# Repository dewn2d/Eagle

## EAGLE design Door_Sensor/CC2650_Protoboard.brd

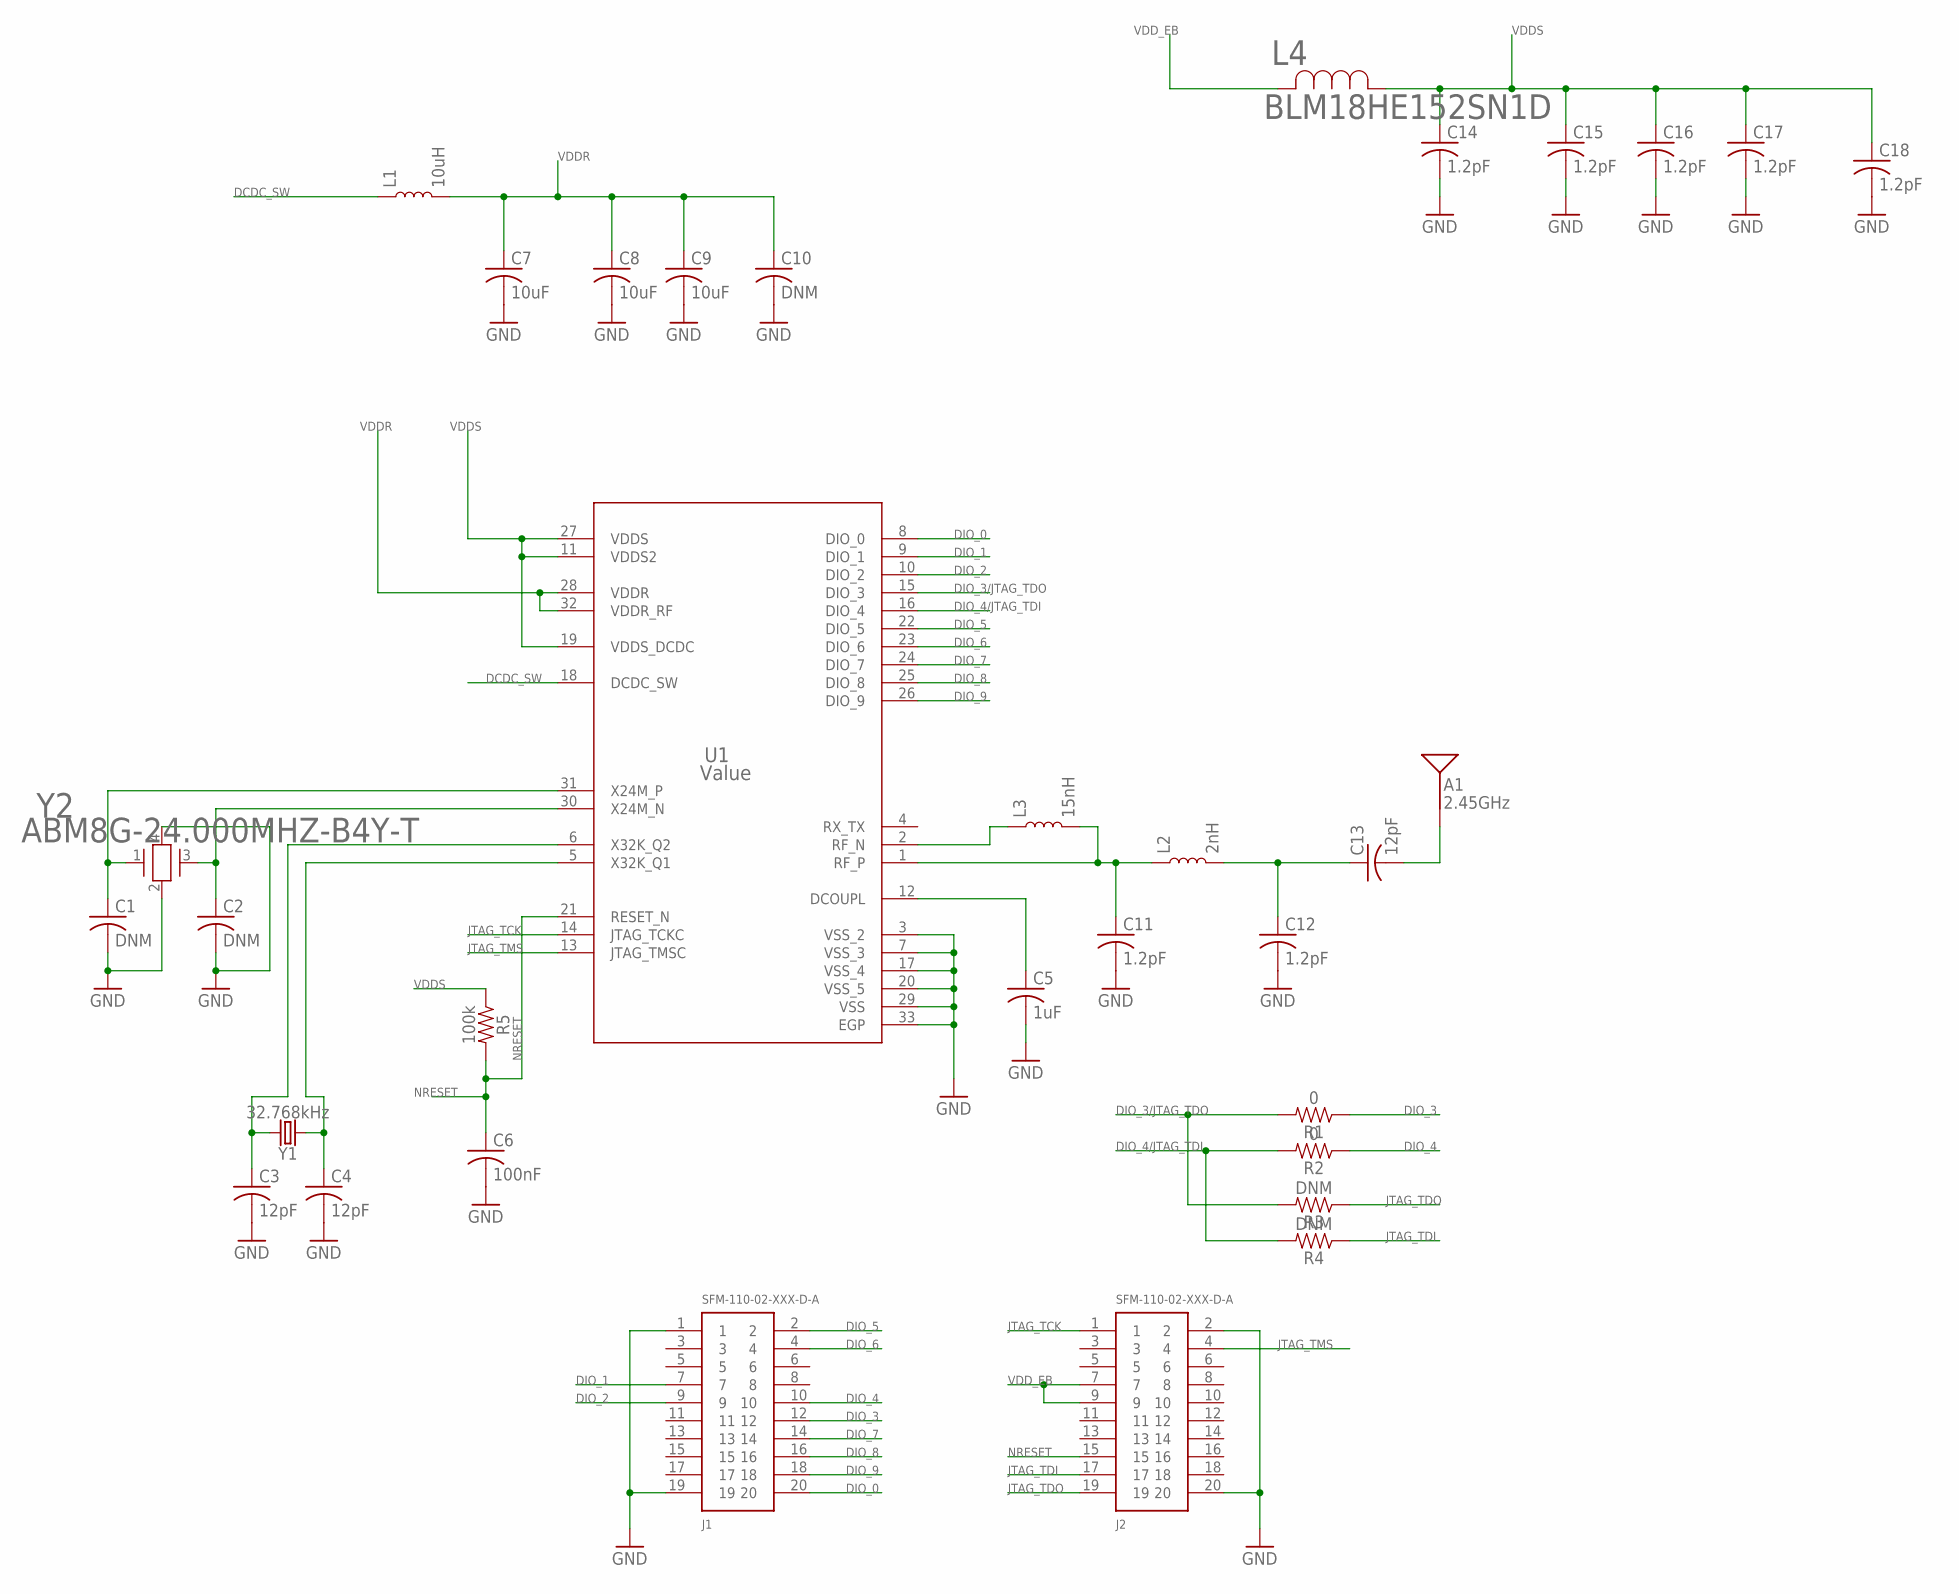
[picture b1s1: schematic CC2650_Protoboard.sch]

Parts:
A1: 2.45GHz; ANT-2.4GHZ-6.5X2.2MM
C1, C2, C10: DNM; C0402
C3, C4, C13: 12pF; C0402
C5: 1uF; C0402
C6: 100nF; C0402
C7, C8, C9: 10uF; C0402
C11, C12, C14, C15, C16, C17, C18: 1.2pF; C0402
J1, J2: SFM-110-02-XXX-D-A
L1: 10uH; 0402
L2: 2nH; 0402
L3: 15nH; 0402
L4: BLM18HE152SN1D; IND_BLM18_0603
R1, R2: 0; 0603
R3, R4: DNM; 0603
R5: 100k; 0603
U1: Value; RSM0032B
Y1: 32.768kHz; CRYSTAL-SMD-3.2X1.5MM
Y2: ABM8G-24.000MHZ-B4Y-T; CRYSTAL_ABM8G

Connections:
DCDC_SW: L1.1, U1.18 (DCDC_SW)
DIO_0: J1.20, U1.8 (DIO_0)
DIO_1: J1.7, U1.9 (DIO_1)
DIO_2: J1.9, U1.10 (DIO_2)
DIO_3: J1.12, R1.1
DIO_3/JTAG_TDO: R1.2, R3.2, U1.15 (DIO_3)
DIO_4: J1.10, R2.1
DIO_4/JTAG_TDI: R2.2, R4.2, U1.16 (DIO_4)
DIO_5: J1.2, U1.22 (DIO_5)
DIO_6: J1.4, U1.23 (DIO_6)
DIO_7: J1.14, U1.24 (DIO_7)
DIO_8: J1.16, U1.25 (DIO_8)
DIO_9: J1.18, U1.26 (DIO_9)
GND: C1.2, C2.2, C3.2, C4.2, C5.2, C6.2, C7.2, C8.2, C9.2, C10.2, C11.2, C12.2, C14.2, C15.2, C16.2, C17.2, C18.2, J1.1, J1.19, J2.2, J2.20, U1.3 (VSS_2), U1.7 (VSS_3), U1.17 (VSS_4), U1.20 (VSS_5), U1.29 (VSS), U1.33 (EGP), Y2.2, Y2.4
JTAG_TCK: J2.1, U1.14 (JTAG_TCKC)
JTAG_TDI: J2.17, R4.1
JTAG_TDO: J2.19, R3.1
JTAG_TMS: J2.4, U1.13 (JTAG_TMSC)
unnamed: C3.1, U1.6 (X32K_Q2), Y1.P$2 (2)
unnamed: C4.1, U1.5 (X32K_Q1), Y1.P$1 (1)
unnamed: C2.1, U1.30 (X24M_N), Y2.3
unnamed: C1.1, U1.31 (X24M_P), Y2.1
unnamed: C5.1, U1.12 (DCOUPL)
unnamed: C11.1, L2.1, L3.2, U1.1 (RF_P)
unnamed: C12.1, C13.1, L2.2
unnamed: A1.FEED, C13.2
unnamed: L3.1, U1.2 (RF_N)
NRESET: C6.1, J2.15, R5.2, U1.21 (RESET_N)
VDDR: C7.1, C8.1, C9.1, C10.1, L1.2, U1.28 (VDDR), U1.32 (VDDR_RF)
VDDS: C14.1, C15.1, C16.1, C17.1, C18.1, L4.1, R5.1, U1.11 (VDDS2), U1.19 (VDDS_DCDC), U1.27 (VDDS)
VDD_EB: J2.7, J2.9, L4.2

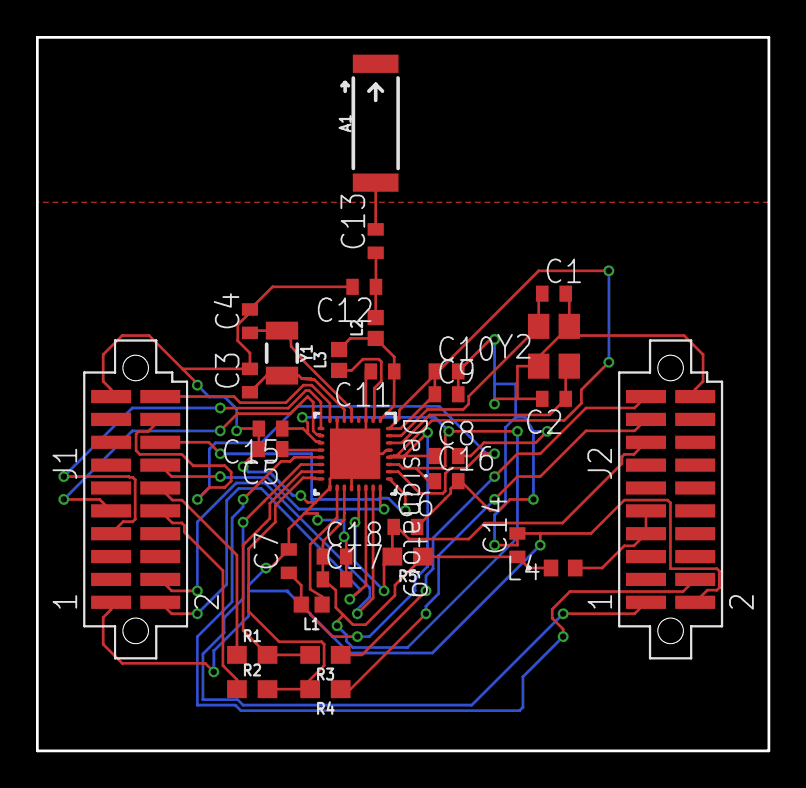
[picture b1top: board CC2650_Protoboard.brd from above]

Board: 2 copper layers, 40.6 x 39.6 mm, 33 parts (0 on the bottom side), 31 nets.

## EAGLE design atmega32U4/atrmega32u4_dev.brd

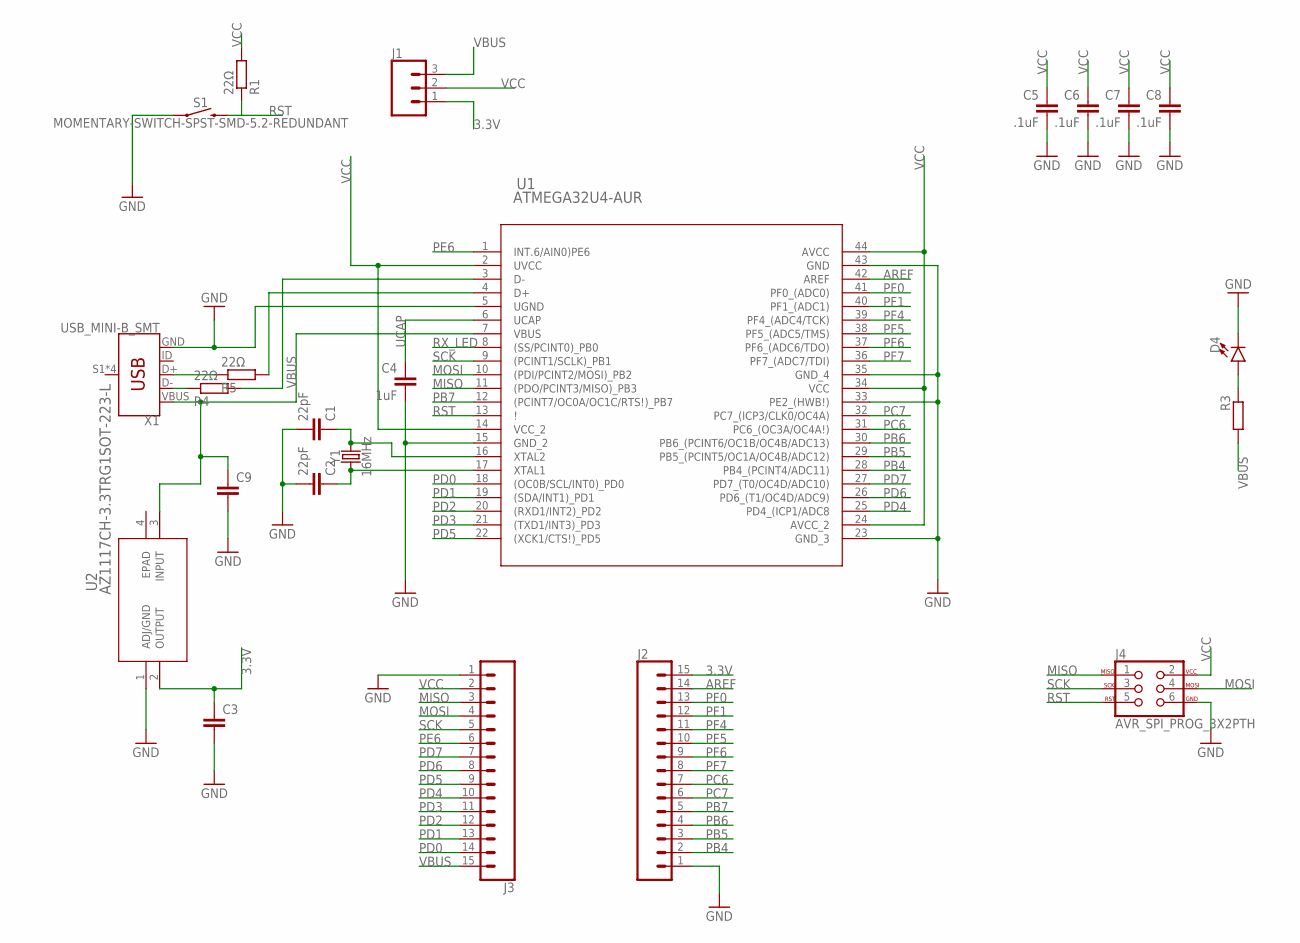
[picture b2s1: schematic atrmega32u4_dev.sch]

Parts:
C1, C2: 22pF; C0603
C3, C9: C-EUC0603; C0603
C4: 1uF; C0603
C5, C6, C7, C8: .1uF; C0603
D4: LED0603; LED-0603
J1: CONN_03; 1X03
J2, J3: CONN_15; 1X15
J4: AVR_SPI_PROG_3X2PTH; 2X3
R1, R4, R5: 22Ω; R0603
R3: R-EU_R0603; R0603
S1: MOMENTARY-SWITCH-SPST-SMD-5.2-REDUNDANT; TACTILE_SWITCH_SMD_5.2MM
U1: ATMEGA32U4-AUR; 44ML
U2: AZ1117CH-3.3TRG1SOT-223-L; SOT-223-L
X1: USB_MINI-B_SMT; USB-MINIB
Y1: 16MHz; CRYSTAL-SMD-5X3.2-4PAD

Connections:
3.3V: C3.1, J1.1, J2.15, U2.2 (OUTPUT)
AREF: J2.14, U1.42 (AREF)
D+: R5.2, U1.4 (D+)
D-: R4.2, U1.3 (D-)
GND: C1.2, C2.2, C3.2, C4.2, C5.2, C6.2, C7.2, C8.2, C9.2, D4.C, J2.1, J3.1, J4.6, S1.1, S1.2 (1), U1.5 (UGND), U1.15 (GND_2), U1.23 (GND_3), U1.33 (PE2_(HWB!)), U1.35 (GND_4), U1.43 (GND), U2.1 (ADJ/GND), X1.GND
MISO: J3.3, J4.1, U1.11 ((PDO/PCINT3/MISO)_PB3)
MOSI: J3.4, J4.4, U1.10 ((PDI/PCINT2/MOSI)_PB2)
unnamed: R5.1, X1.D+
unnamed: D4.A, R3.1
unnamed: C1.1, U1.16 (XTAL2), Y1.1
unnamed: C2.1, U1.17 (XTAL1), Y1.3 (2)
unnamed: R4.1, X1.D-
PB4: J2.2, U1.28 (PB4_(PCINT4/ADC11))
PB5: J2.3, U1.29 (PB5_(PCINT5/OC1A/OC4B/ADC12))
PB6: J2.4, U1.30 (PB6_(PCINT6/OC1B/OC4B/ADC13))
PB7: J2.5, U1.12 ((PCINT7/OC0A/OC1C/RTS!)_PB7)
PC6: J2.7, U1.31 (PC6_(OC3A/OC4A!))
PC7: J2.6, U1.32 (PC7_(ICP3/CLK0/OC4A))
PD0: J3.14, U1.18 ((OC0B/SCL/INT0)_PD0)
PD1: J3.13, U1.19 ((SDA/INT1)_PD1)
PD2: J3.12, U1.20 ((RXD1/INT2)_PD2)
PD3: J3.11, U1.21 ((TXD1/INT3)_PD3)
PD4: J3.10, U1.25 (PD4_(ICP1/ADC8)
PD5: J3.9, U1.22 ((XCK1/CTS!)_PD5)
PD6: J3.8, U1.26 (PD6_(T1/OC4D/ADC9))
PD7: J3.7, U1.27 (PD7_(T0/OC4D/ADC10))
PE6: J3.6, U1.1 (INT.6/AIN0)PE6)
PF0: J2.13, U1.41 (PF0_(ADC0))
PF1: J2.12, U1.40 (PF1_(ADC1))
PF4: J2.11, U1.39 (PF4_(ADC4/TCK))
PF5: J2.10, U1.38 (PF5_(ADC5/TMS))
PF6: J2.9, U1.37 (PF6_(ADC6/TDO))
PF7: J2.8, U1.36 (PF7_(ADC7/TDI))
RST: J4.5, R1.1, S1.3 (2), S1.4 (2), U1.13 (!)
RX_LED: U1.8 ((SS/PCINT0)_PB0)
SCK: J3.5, J4.3, U1.9 ((PCINT1/SCLK)_PB1)
UCAP: C4.1, U1.6 (UCAP)
VBUS: C9.1, J1.3, J3.15, R3.2, U1.7 (VBUS), U2.3 (INPUT), X1.VBUS
VCC: C5.1, C6.1, C7.1, C8.1, J1.2, J3.2, J4.2, R1.2, U1.2 (UVCC), U1.14 (VCC_2), U1.24 (AVCC_2), U1.34 (VCC), U1.44 (AVCC)

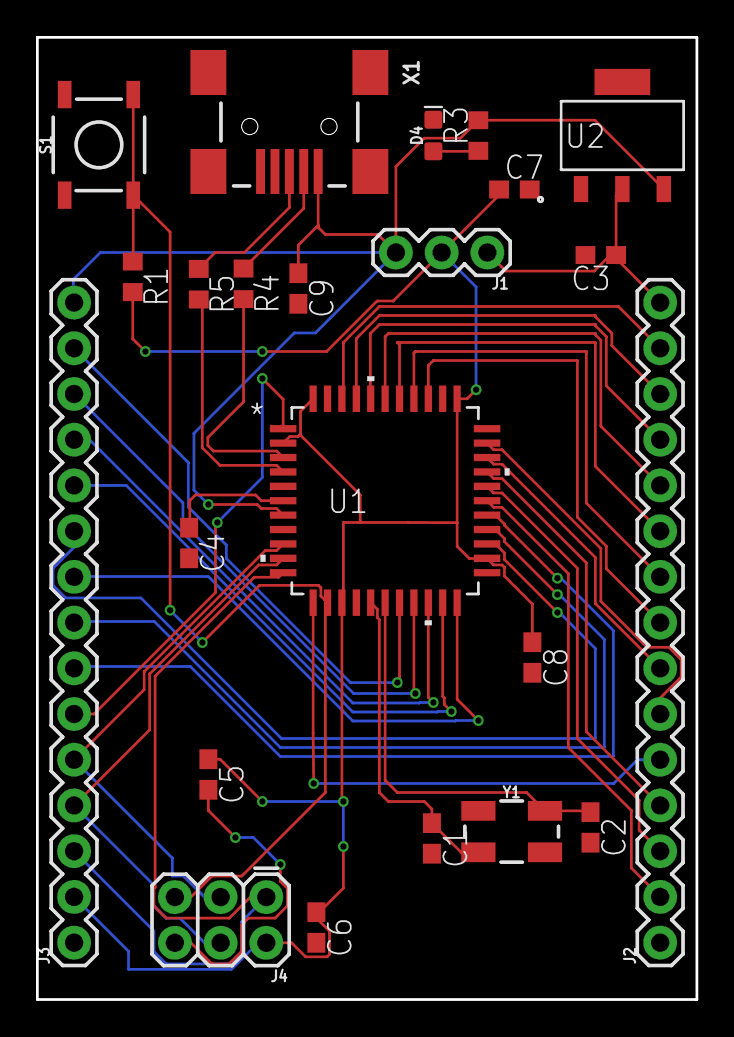
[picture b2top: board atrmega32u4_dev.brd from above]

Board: 2 copper layers, 36.6 x 53.5 mm, 23 parts (0 on the bottom side), 38 nets.

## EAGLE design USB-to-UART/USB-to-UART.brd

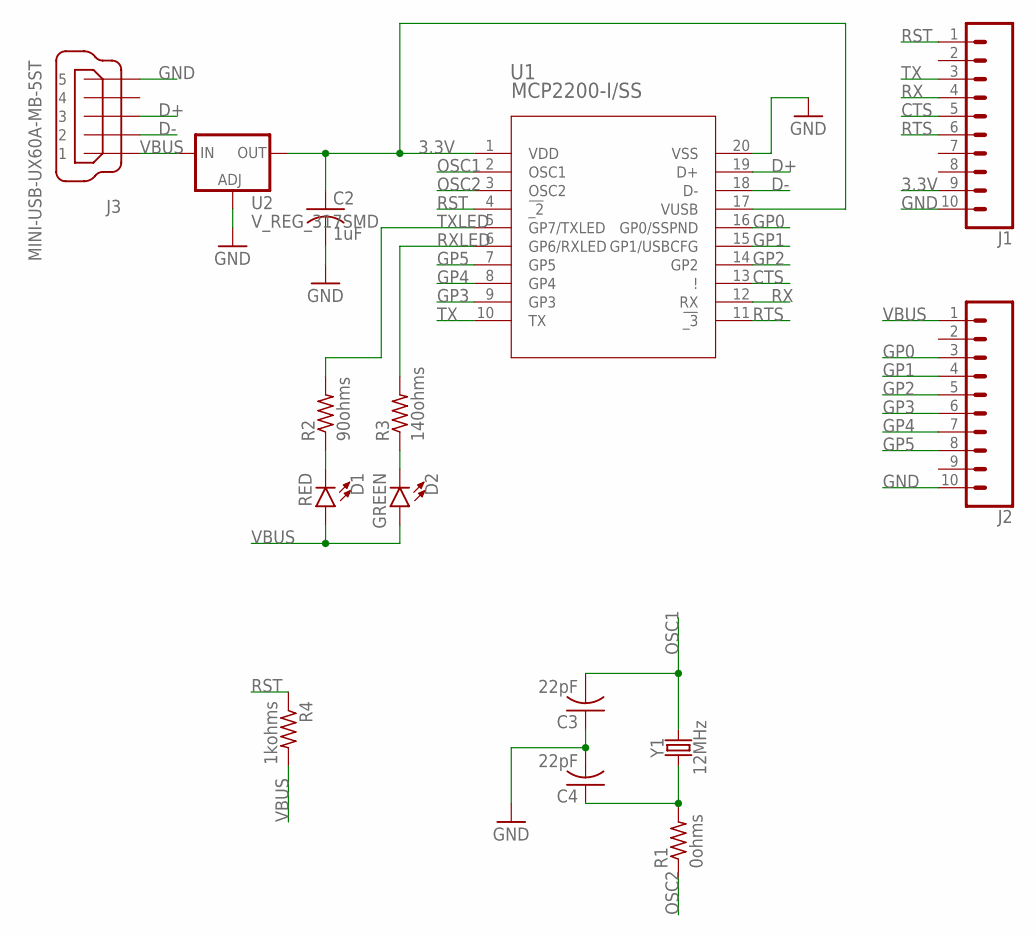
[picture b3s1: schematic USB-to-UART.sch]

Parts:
C2: 1uF; C0603
C3, C4: 22pF; C0603
D1: RED; LED-0603
D2: GREEN; LED-0603
J1, J2: CONN_10"; 1X10
J3: MINI-USB-UX60A-MB-5ST; UX60A-MB-5ST
R1: 0ohms; R0603
R2: 90ohms; R0603
R3: 140ohms; R0603
R4: 1kohms; R0603
U1: MCP2200-I/SS; SSOP20_MC
U2: V_REG_317SMD; SOT223
Y1: 12MHz; CRYSTAL-SMD-5X3.2-4PAD

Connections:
3.3V: C2.1, J1.9, U1.1 (VDD), U1.17 (VUSB), U2.2 (OUT)
CTS: J1.5, U1.13 (!)
D+: J3.3, U1.19 (D+)
D-: J3.2, U1.18 (D-)
GND: C2.2, C3.1, C4.2, J1.10, J2.10, J3.5, U1.20 (VSS), U2.1 (ADJ)
GP0: J2.3, U1.16 (GP0/SSPND)
GP1: J2.4, U1.15 (GP1/USBCFG)
GP2: J2.5, U1.14 (GP2)
GP3: J2.6, U1.9 (GP3)
GP4: J2.7, U1.8 (GP4)
GP5: J2.8, U1.7 (GP5)
unnamed: D1.C, R2.1
unnamed: C4.1, R1.2, Y1.1
unnamed: D2.C, R3.1
OSC1: C3.2, U1.2 (OSC1), Y1.3 (2)
OSC2: R1.1, U1.3 (OSC2)
RST: J1.1, R4.1, U1.4 (!_2)
RTS: J1.6, U1.11 (!_3)
RX: J1.4, U1.12 (RX)
RXLED: R3.2, U1.6 (GP6/RXLED)
TX: J1.3, U1.10 (TX)
TXLED: R2.2, U1.5 (GP7/TXLED)
VBUS: D1.A, D2.A, J2.1, J3.1, R4.2, U2.3 (IN)

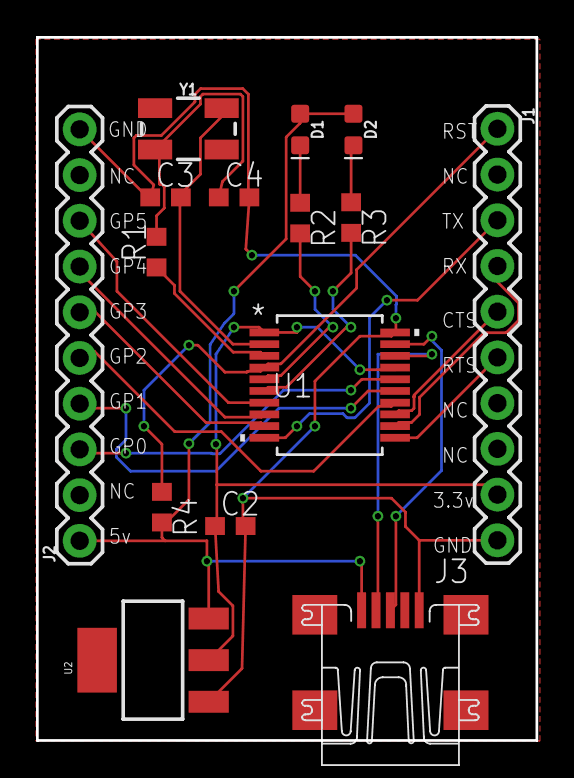
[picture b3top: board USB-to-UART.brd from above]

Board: 2 copper layers, 27.8 x 39.1 mm, 15 parts (0 on the bottom side), 23 nets.

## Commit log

2018-05-22 init

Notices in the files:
parts and their libraries:
SparkFun-RF: Licensing: Creative Commons ShareAlike 4.0 International - https://creativecommons.org/licenses/by-sa/4.0
